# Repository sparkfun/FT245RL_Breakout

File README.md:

SparkFun USB to FIFO- FT245RL Breakout
========================================

[*SparkFun USB to FIFO- FT245RL Breakout (BOB-07841)*](https://www.sparkfun.com/products/7841)

Basic breakout board for FTDI’s popular USB to FIFO IC. 

Repository Contents
-------------------
* **/Hardware** - All Eagle design files (.brd, .sch, .STL)

License Information
-------------------
The hardware is released under [Creative Commons ShareAlike 4.0 International](https://creativecommons.org/licenses/by-sa/4.0/).

Distributed as-is; no warranty is given.

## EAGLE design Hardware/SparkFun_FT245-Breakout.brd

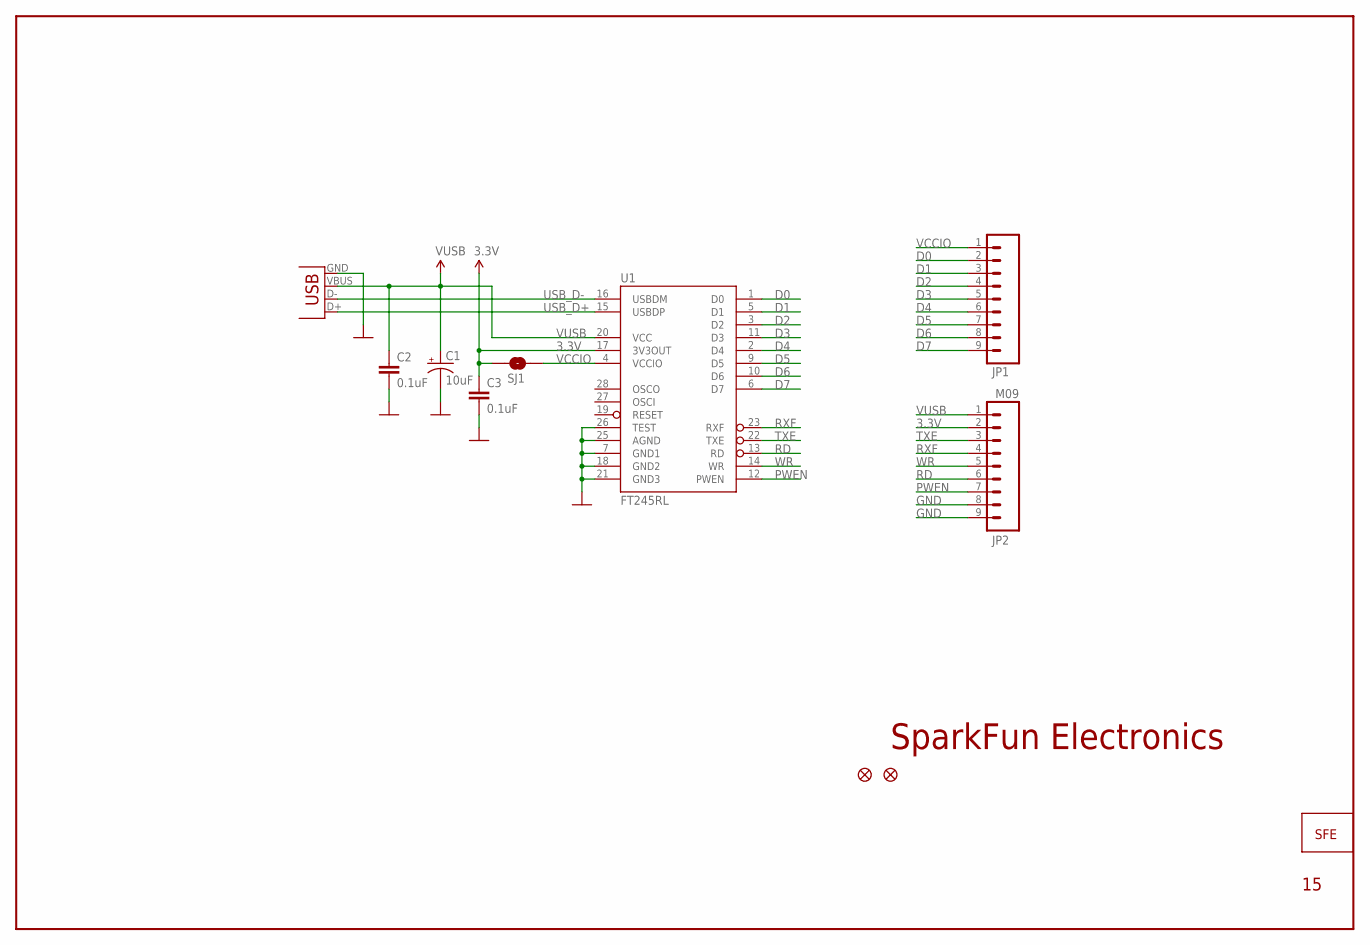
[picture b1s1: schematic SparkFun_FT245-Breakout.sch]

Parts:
C1: 10uF; CPOL_1206
C2, C3: 0.1uF; 0402-CAP
JP1, JP2: M09; 1X09
JP3, JP4: FIDUCIAL1X2; FIDUCIAL-1X2
SJ1: SOLDERJUMPERNC2; SJ_2S-NOTRACE
U1: FT245RL; SSOP28DB
U$1: LOGO-SFENEW; SFE-NEW-WEBLOGO
X2: USBSMD; USB-MINIB

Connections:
3.3V: C3.1, JP2.2, SJ1.1, U1.17 (3V3OUT)
D0: JP1.2, U1.1 (D0)
D1: JP1.3, U1.5 (D1)
D2: JP1.4, U1.3 (D2)
D3: JP1.5, U1.11 (D3)
D4: JP1.6, U1.2 (D4)
D5: JP1.7, U1.9 (D5)
D6: JP1.8, U1.10 (D6)
D7: JP1.9, U1.6 (D7)
GND: C1.C (-), C2.2, C3.2, JP2.8, JP2.9, U1.7 (GND1), U1.18 (GND2), U1.21 (GND3), U1.25 (AGND), U1.26 (TEST), X2.GND
PWEN: JP2.7, U1.12 (PWEN)
RD: JP2.6, U1.13 (RD)
RXF: JP2.4, U1.23 (RXF)
TXE: JP2.3, U1.22 (TXE)
USB_D+: U1.15 (USBDP), X2.D+
USB_D-: U1.16 (USBDM), X2.D-
VCCIO: JP1.1, SJ1.2, U1.4 (VCCIO)
VUSB: C1.A (+), C2.1, JP2.1, U1.20 (VCC), X2.VBUS
WR: JP2.5, U1.14 (WR)

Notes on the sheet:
SparkFun Electronics

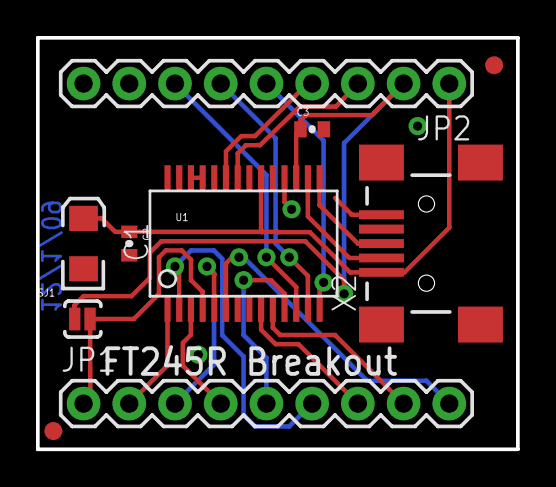
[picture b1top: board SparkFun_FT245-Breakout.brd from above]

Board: 2 copper layers, 26.7 x 22.9 mm, 11 parts (1 on the bottom side), 19 nets.

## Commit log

2015-01-29 Initial hardware commit
